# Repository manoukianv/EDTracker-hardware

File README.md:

# EDTracker-hardware
EDTracker Hardware : PCB &amp; 3DBox

Based on the great project : http://www.edtracker.org.uk
This is not the official board, some restriction can be found.

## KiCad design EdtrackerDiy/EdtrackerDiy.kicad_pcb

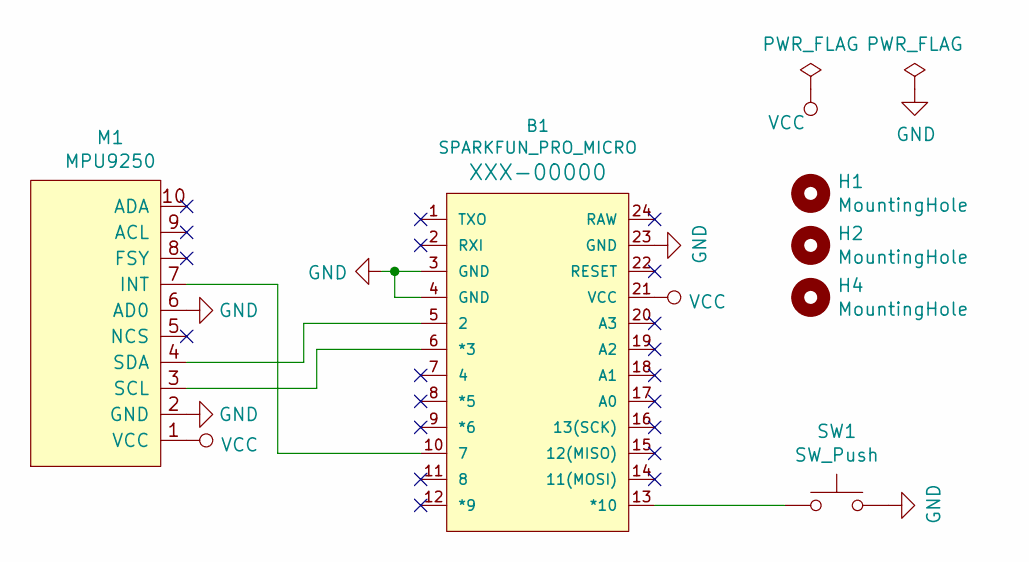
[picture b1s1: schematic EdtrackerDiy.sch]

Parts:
B1: SPARKFUN_PRO_MICRO
H1, H2, H4: MountingHole; MountingHole_3.2mm_M3
M1: MPU9250
SW1: SW_Push; SW_PUSH_6mm_H8mm

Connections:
GND: B1.3 (GND), B1.4 (GND), B1.23 (GND), M1.2 (GND), M1.6 (AD0), SW1.2
unnamed: B1.5 (2), M1.4 (SDA)
unnamed: B1.6 (*3), M1.3 (SCL)
unnamed: B1.10 (7), M1.7 (INT)
unnamed: B1.13 (*10), SW1.1
VCC: B1.21 (VCC), M1.1 (VCC)

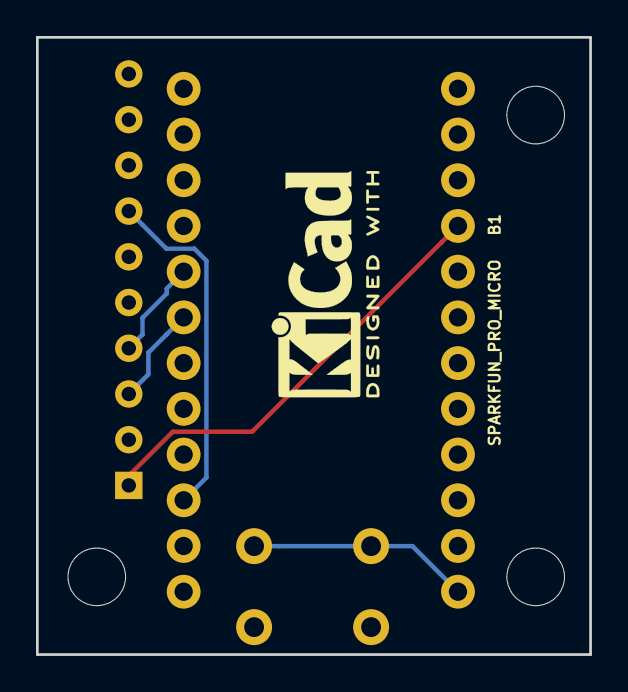
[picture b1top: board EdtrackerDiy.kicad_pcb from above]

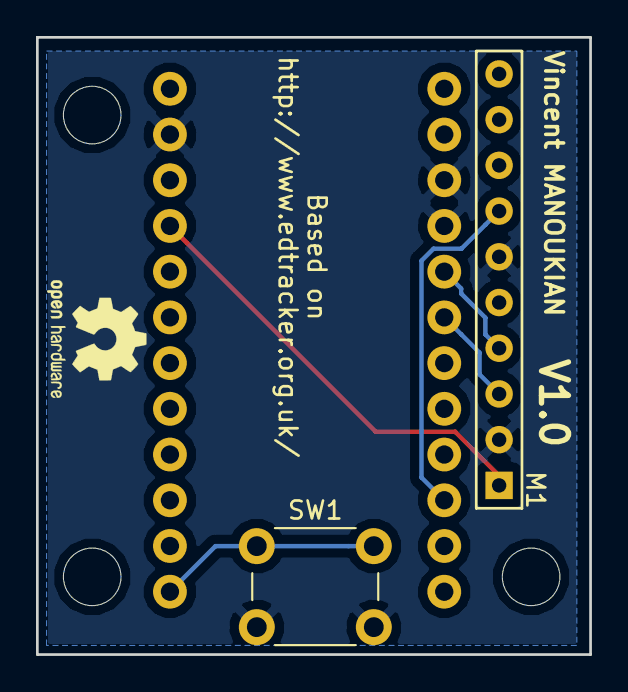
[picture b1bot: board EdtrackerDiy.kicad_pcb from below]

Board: 2 copper layers, 30.7 x 34.3 mm, 6 parts (2 on the bottom side), 6 nets.

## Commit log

2018-12-26 Initial creation
